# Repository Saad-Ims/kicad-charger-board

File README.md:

# Project Overview

I made a lighting control system using **KiCad** and **Fusion 360**.

## How to Open the Project

To open this project:
1. Download or clone this repository.
2. Install [KiCad](https://www.kicad.org/).
3. Open the `.kicad_pro` project file.
4. Explore the schematic and PCB layout.
5. Make modifications or improve the design.

## How Does It Work?

The system can receive electrical power from different sources:
- **Outlet:** The main power source.
- **Solar panel:** Provides power using sunlight.
- **Wind generator:** Can also be connected as an alternative renewable energy source.

Once powered, the system uses a **photoresistor** to detect the surrounding light level.
An **ATtiny microcontroller** processes the sensor readings and controls a relay, which automatically switches the light ON or OFF.
After designing and developing the electronic circuit, I designed the PCB using **KiCad**. Once the PCB design was completed, I moved on to creating a custom enclosure using **Fusion 360**.

## Tools I used

- **KiCad:** Schematic and PCB design.
- **Fusion 360:** 3D designing.

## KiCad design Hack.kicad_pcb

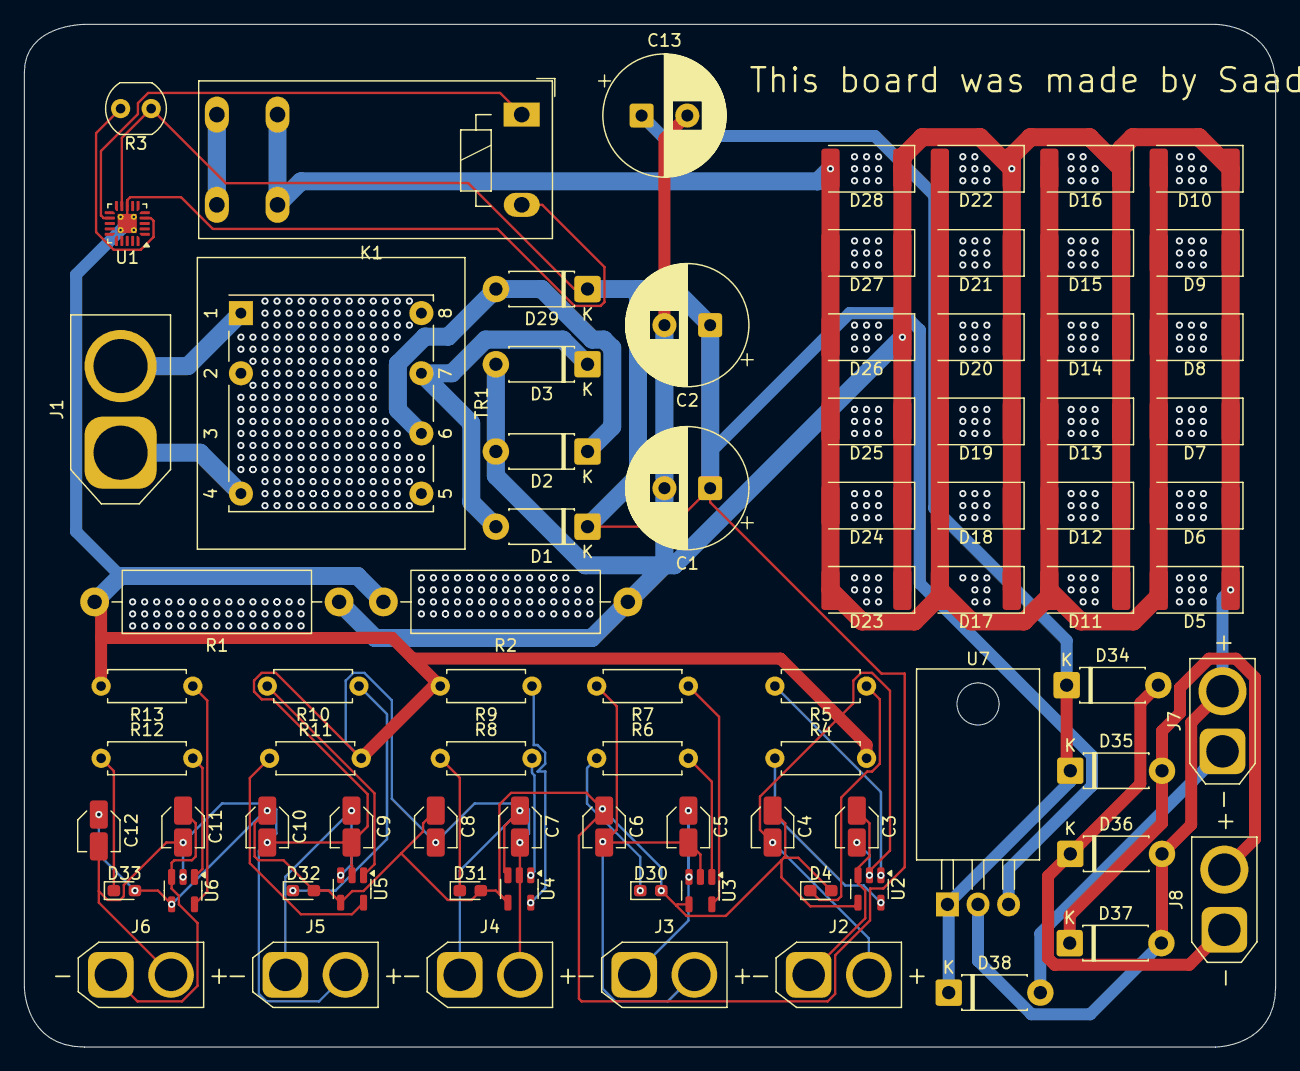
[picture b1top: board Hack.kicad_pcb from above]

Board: 2 copper layers, 104.0 x 85.0 mm, 81 parts (0 on the bottom side), 35 nets.

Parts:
C1, C2, C13: C_Polarized; CP_Radial_D10.0mm_P3.80mm
C3, C4, C5, C6, C7, C8, C9, C10, C11, C12: C; C_Elec_3x5.4
D1, D2, D3, D29, D34, D35, D36, D37, D38: 1N4001; D_DO-41_SOD81_P7.62mm_Horizontal
D4, D30, D31, D32, D33: LED; LED_0603_1608Metric_Pad1.05x0.95mm_HandSolder
D5, D6, D7, D8, D9, D10, D11, D12, D13, D14, D15, D16, D17, D18, D19, D20, D21, D22, D23, D24, D25, D26, D27, D28: LED; LED_2512_6332Metric_Pad1.52x3.35mm_HandSolder
J1: Conn_01x02_Socket; AMASS_XT60-M_1x02_P7.20mm_Vertical
J2, J3, J4, J5, J6: Conn_01x02_Pin; AMASS_XT30U-M_1x02_P5.0mm_Vertical
J7, J8: Conn_01x02_Pin; AMASS_XT30U-F_1x02_P5.0mm_Vertical
K1: Relay_SPST-NC; Relay_SPST_Schrack-RT1-16A-FormA_RM5mm
R1, R2: R; R_Axial_DIN0516_L15.5mm_D5.0mm_P20.32mm_Horizontal
R3: R_Photo; R_LDR_4.9x4.2mm_P2.54mm_Vertical
R4, R5, R6, R7, R8, R9, R10, R11, R12, R13: R; R_Axial_DIN0207_L6.3mm_D2.5mm_P7.62mm_Horizontal
TR1: TEZ0.5-D-1; Transformer_Breve_TEZ-22x24
U1: ATtiny20-MM; QFN-20-1EP_3x3mm_P0.45mm_EP1.6x1.6mm_ThermalVias
U2, U3, U4, U5, U6: MCP73831-2-OT; SOT-23-5
U7: LM7818_TO220; TO-220-3_Horizontal_TabDown

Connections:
unnamed: D1.2 (A), D3.1 (K), TR1.7
unnamed: C1.1, C2.1, C4.1, C6.1, C8.1, C10.1, C12.1, D1.1 (K), D4.2 (A), D29.1 (K), D30.2 (A), D31.2 (A), D32.2 (A), D33.2 (A), R3.1, U1.9 (VCC), U2.4 (V_{DD}), U3.4 (V_{DD}), U4.4 (V_{DD}), U5.4 (V_{DD}), U6.4 (V_{DD}), U7.3 (VO)
unnamed: D2.1 (K), D29.2 (A), TR1.6
unnamed: D4.1 (K), R5.1
unnamed: D5.2 (A), D6.2 (A), D7.2 (A), D8.2 (A), D9.2 (A), D10.2 (A), D11.2 (A), D12.2 (A), D13.2 (A), D14.2 (A), D15.2 (A), D16.2 (A), D17.2 (A), D18.2 (A), D19.2 (A), D20.2 (A), D21.2 (A), D22.2 (A), D23.2 (A), D24.2 (A), D25.2 (A), D26.2 (A), D27.2 (A), D28.2 (A), K1.11
unnamed: C1.2, C2.2, C13.2, D2.2 (A), D3.2 (A), D5.1 (K), D6.1 (K), D7.1 (K), D8.1 (K), D9.1 (K), D10.1 (K), D11.1 (K), D12.1 (K), D13.1 (K), D14.1 (K), D15.1 (K), D16.1 (K), D17.1 (K), D18.1 (K), D19.1 (K), D20.1 (K), D21.1 (K), D22.1 (K), D23.1 (K), D24.1 (K), D25.1 (K), D26.1 (K), D27.1 (K), D28.1 (K), D36.2 (A), D37.2 (A), J7.2, R1.1, R2.1, U7.2 (GND)
unnamed: D30.1 (K), R6.1
unnamed: D31.1 (K), R8.1
unnamed: D32.1 (K), R10.1
unnamed: D33.1 (K), R12.1
unnamed: D34.2 (A), D36.1 (K), J8.1
unnamed: C13.1, D34.1 (K), D35.1 (K), D38.1 (K), U7.1 (VI)
unnamed: D35.2 (A), D37.1 (K), J8.2
unnamed: D38.2 (A), J7.1
unnamed: J1.1, TR1.4
unnamed: J1.2, TR1.1
unnamed: C3.1, J2.1, U2.3 (V_{BAT})
unnamed: C3.2, C4.2, C7.2, C8.2, C9.2, C10.2, C11.2, C12.2, J2.2, J4.2, J5.2, J6.2, K1.A2, R1.2, R2.2, R4.2, R9.2, R11.2, R13.2, U1.8 (GND), U1.21 (GND), U2.2 (V_{SS}), U4.2 (V_{SS}), U5.2 (V_{SS}), U6.2 (V_{SS})
unnamed: C5.1, J3.1, U3.3 (V_{BAT})
unnamed: C5.2, C6.2, J3.2, R7.2, U3.2 (V_{SS})
unnamed: C7.1, J4.1, U4.3 (V_{BAT})
unnamed: C9.1, J5.1, U5.3 (V_{BAT})
unnamed: C11.1, J6.1, U6.3 (V_{BAT})
unnamed: R3.2, U1.4 (PA1)
unnamed: K1.A1, U1.12 (PB1)
unnamed: R4.1, U2.5 (PROG)
unnamed: R5.2, U2.1 (STAT)
unnamed: R7.1, U3.5 (PROG)
unnamed: R6.2, U3.1 (STAT)
unnamed: R9.1, U4.5 (PROG)
unnamed: R8.2, U4.1 (STAT)
unnamed: R11.1, U5.5 (PROG)
unnamed: R10.2, U5.1 (STAT)
unnamed: R13.1, U6.5 (PROG)
unnamed: R12.2, U6.1 (STAT)
